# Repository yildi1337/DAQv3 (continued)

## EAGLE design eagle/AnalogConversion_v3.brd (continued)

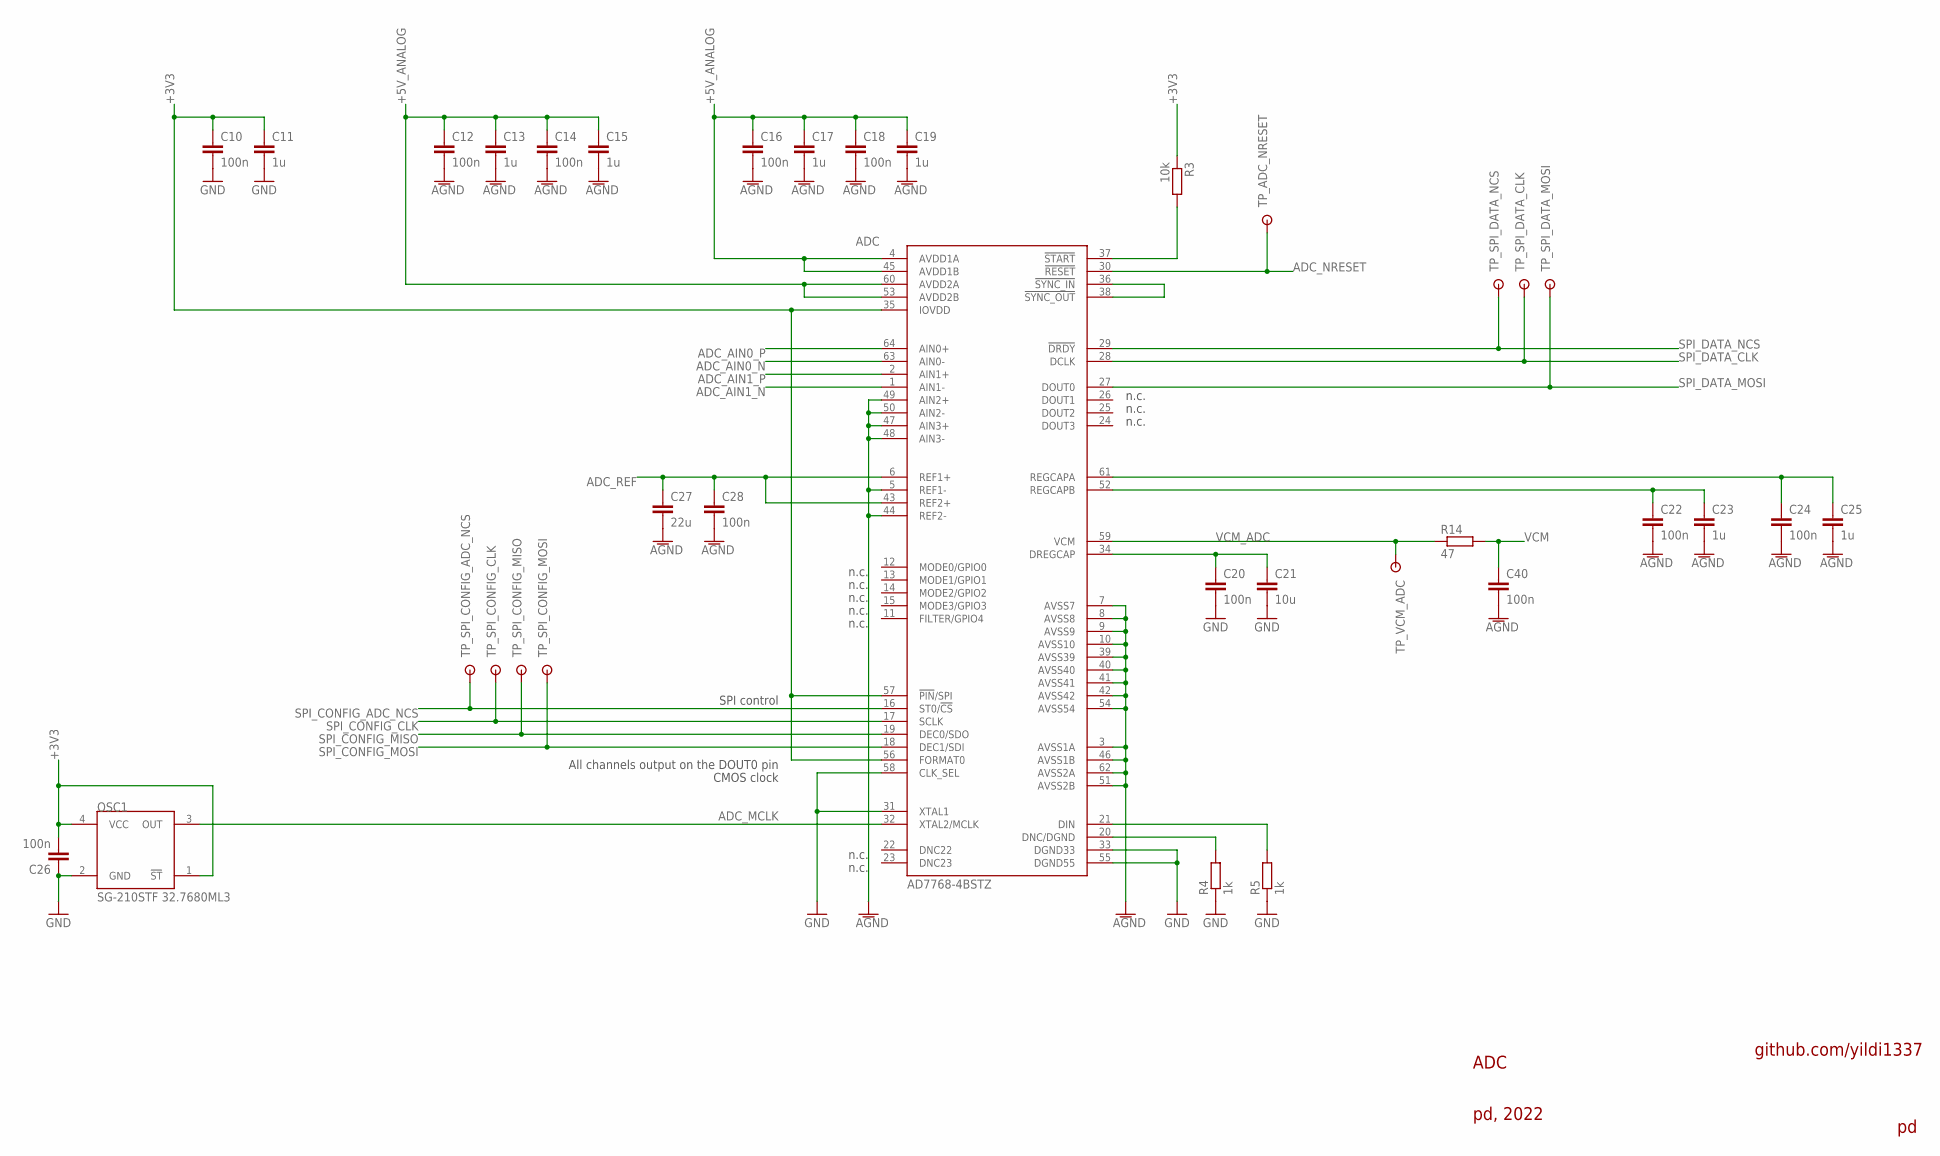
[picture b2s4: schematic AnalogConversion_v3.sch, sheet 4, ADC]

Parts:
ADC: AD7768-4BSTZ
C10, C12, C14, C16, C18, C20, C22, C24, C26, C28, C40: 100n; C0603
C11, C13, C15, C17, C19, C23, C25: 1u; C0603
C21: 10u; C0603
C27: 22u; C1206
OSC1: SG-210STF 32.7680ML3; SG-210STF-32.7680ML3
R3: 10k; R0603
R4, R5: 1k; R0603
R14: 47; R0603
TP_ADC_NRESET: RSPRO-1MM-TERMINAL-POST-2622034
TP_SPI_CONFIG_ADC_NCS: RSPRO-1MM-TERMINAL-POST-2622034
TP_SPI_CONFIG_CLK: RSPRO-1MM-TERMINAL-POST-2622034
TP_SPI_CONFIG_MISO: RSPRO-1MM-TERMINAL-POST-2622034
TP_SPI_CONFIG_MOSI: RSPRO-1MM-TERMINAL-POST-2622034
TP_SPI_DATA_CLK: RSPRO-1MM-TERMINAL-POST-2622034
TP_SPI_DATA_MOSI: RSPRO-1MM-TERMINAL-POST-2622034
TP_SPI_DATA_NCS: RSPRO-1MM-TERMINAL-POST-2622034
TP_VCM_ADC: RSPRO-1MM-TERMINAL-POST-2622034

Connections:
+3V3: ADC.35 (IOVDD), ADC.56 (FORMAT0), ADC.57 (!PIN!/SPI), C10.1, C11.1, C26.2, OSC1.1 (!ST), OSC1.4 (VCC), R3.1; also elsewhere on the board
+5V_ANALOG: ADC.4 (AVDD1A), ADC.45 (AVDD1B), ADC.53 (AVDD2B), ADC.60 (AVDD2A), C12.1, C13.1, C14.1, C15.1, C16.1, C17.1, C18.1, C19.1; also elsewhere on the board
ADC_AIN0_N: ADC.63 (AIN0-); also elsewhere on the board
ADC_AIN0_P: ADC.64 (AIN0+); also elsewhere on the board
ADC_AIN1_N: ADC.1 (AIN1-); also elsewhere on the board
ADC_AIN1_P: ADC.2 (AIN1+); also elsewhere on the board
ADC_MCLK: ADC.32 (XTAL2/MCLK), OSC1.3 (OUT)
ADC_NRESET: ADC.30 (!RESET!), TP_ADC_NRESET.P$1; also elsewhere on the board
ADC_REF: ADC.6 (REF1+), ADC.43 (REF2+), C27.1, C28.1; also elsewhere on the board
AGND: ADC.3 (AVSS1A), ADC.5 (REF1-), ADC.7 (AVSS7), ADC.8 (AVSS8), ADC.9 (AVSS9), ADC.10 (AVSS10), ADC.39 (AVSS39), ADC.40 (AVSS40), ADC.41 (AVSS41), ADC.42 (AVSS42), ADC.44 (REF2-), ADC.46 (AVSS1B), ADC.47 (AIN3+), ADC.48 (AIN3-), ADC.49 (AIN2+), ADC.50 (AIN2-), ADC.51 (AVSS2B), ADC.54 (AVSS54), ADC.62 (AVSS2A), C12.2, C13.2, C14.2, C15.2, C16.2, C17.2, C18.2, C19.2, C22.2, C23.2, C24.2, C25.2, C27.2, C28.2, C40.2; also elsewhere on the board
DIN: ADC.21 (DIN), R5.2
DNC/DGND: ADC.20 (DNC/DGND), R4.2
DREGCAP: ADC.34 (DREGCAP), C20.1, C21.1
GND: ADC.31 (XTAL1), ADC.33 (DGND33), ADC.55 (DGND55), ADC.58 (CLK_SEL), C10.2, C11.2, C20.2, C21.2, C26.1, OSC1.2 (GND), R4.1, R5.1; also elsewhere on the board
unnamed: ADC.36 (!SYNC_IN!), ADC.38 (!SYNC_OUT!)
unnamed: ADC.37 (!START!), R3.2
REGCAPA: ADC.61 (REGCAPA), C24.1, C25.1
REGCAPB: ADC.52 (REGCAPB), C22.1, C23.1
SPI_CONFIG_ADC_NCS: ADC.16 (ST0/!CS!), TP_SPI_CONFIG_ADC_NCS.P$1; also elsewhere on the board
SPI_CONFIG_CLK: ADC.17 (SCLK), TP_SPI_CONFIG_CLK.P$1; also elsewhere on the board
SPI_CONFIG_MISO: ADC.19 (DEC0/SDO), TP_SPI_CONFIG_MISO.P$1; also elsewhere on the board
SPI_CONFIG_MOSI: ADC.18 (DEC1/SDI), TP_SPI_CONFIG_MOSI.P$1; also elsewhere on the board
SPI_DATA_CLK: ADC.28 (DCLK), TP_SPI_DATA_CLK.P$1; also elsewhere on the board
SPI_DATA_MOSI: ADC.27 (DOUT0), TP_SPI_DATA_MOSI.P$1; also elsewhere on the board
SPI_DATA_NCS: ADC.29 (!DRDY!), TP_SPI_DATA_NCS.P$1; also elsewhere on the board
VCM: C40.1, R14.2; also elsewhere on the board
VCM_ADC: ADC.59 (VCM), R14.1, TP_VCM_ADC.P$1

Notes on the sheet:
ADC
pd, 2022
All channels output on the DOUT0 pin
CMOS clock
n.c.
SPI control
github.com/yildi1337

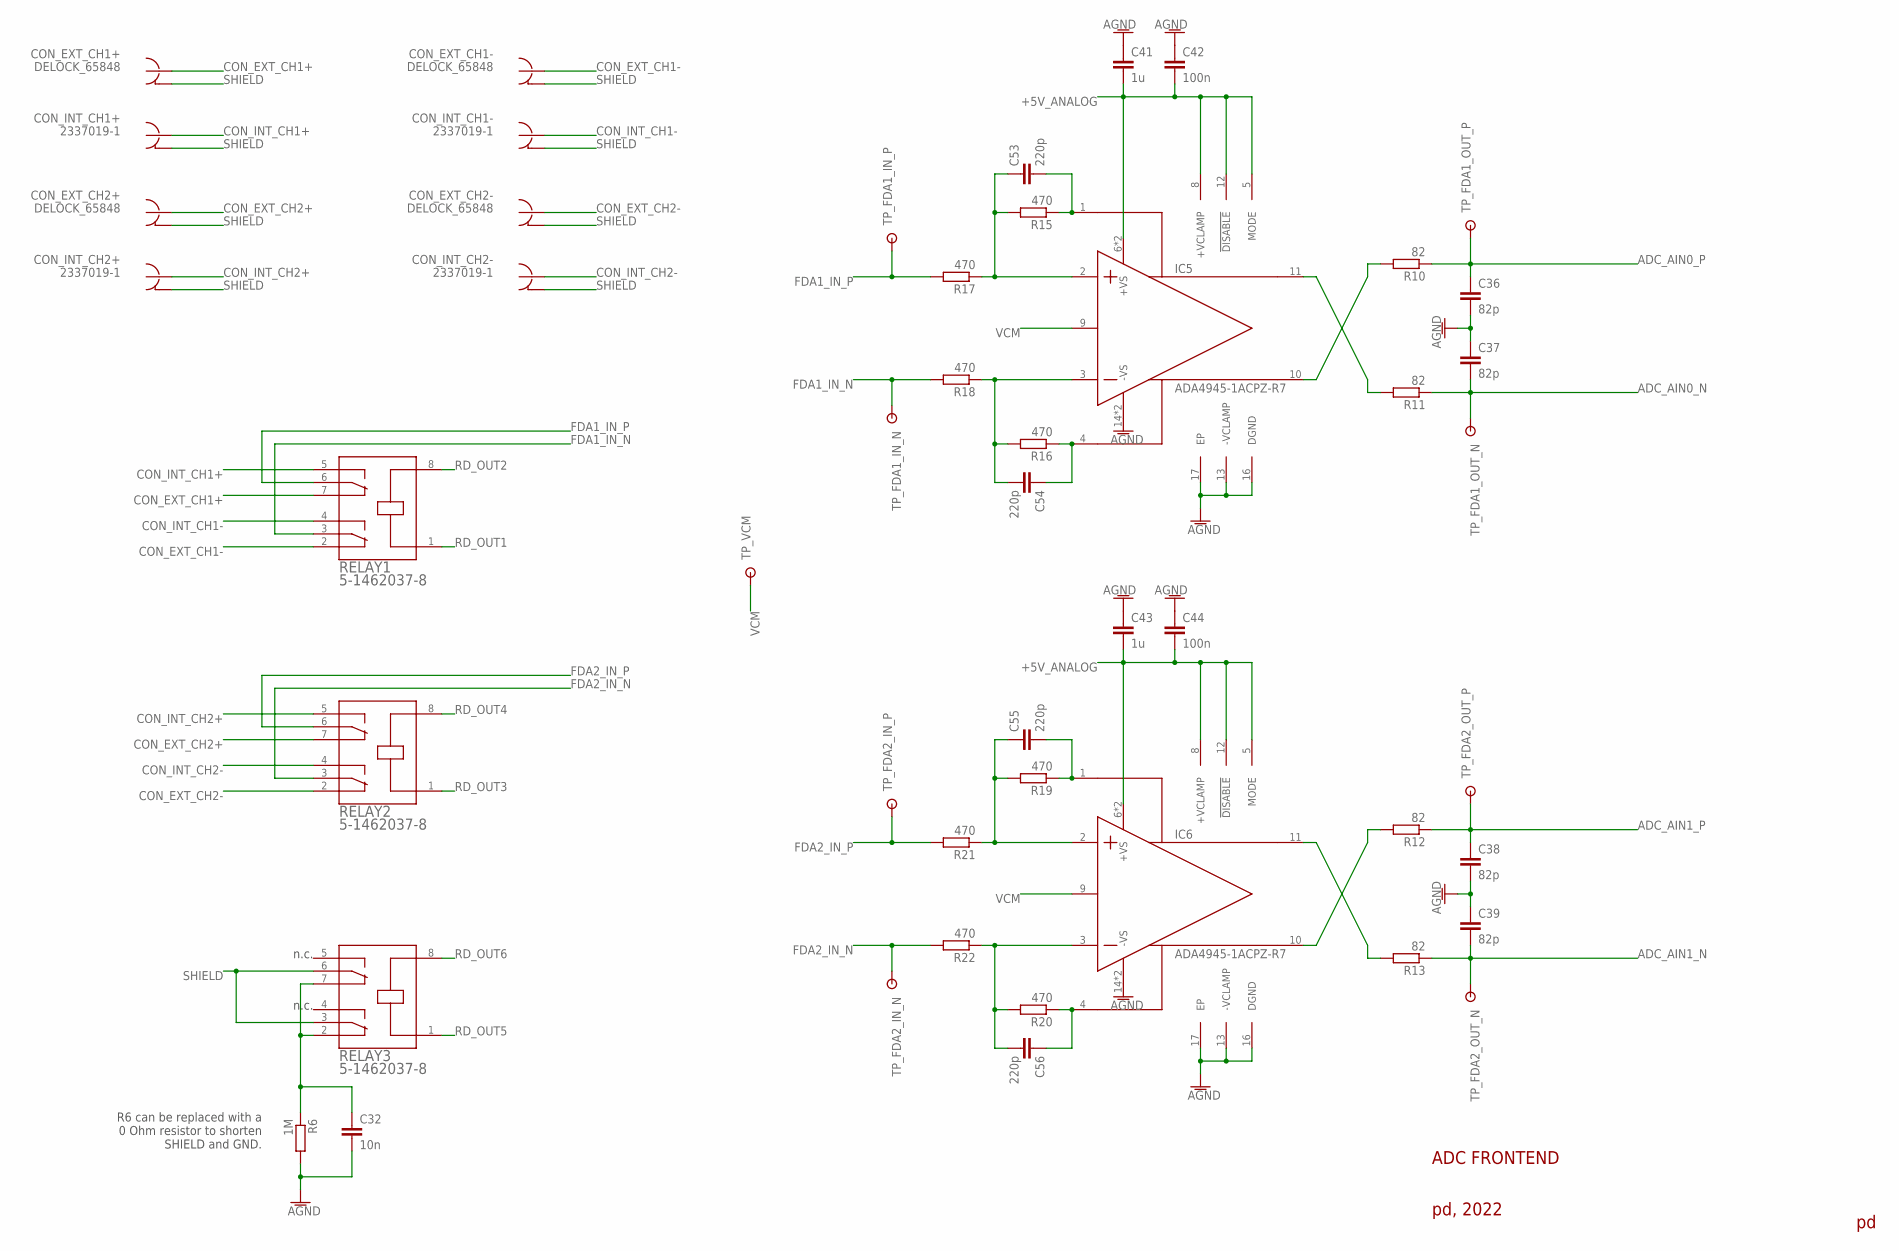
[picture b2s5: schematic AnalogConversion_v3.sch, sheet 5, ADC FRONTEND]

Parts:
C32: 10n; C0603
C36, C37, C38, C39: 82p; C0603
C41, C43: 1u; C0603
C42, C44: 100n; C0603
C53, C54, C55, C56: 220p; C0603
CON_EXT_CH1+, CON_EXT_CH1-, CON_EXT_CH2+, CON_EXT_CH2-: DELOCK_65848
CON_INT_CH1+, CON_INT_CH1-, CON_INT_CH2+, CON_INT_CH2-: 2337019-1
IC5, IC6: ADA4945-1ACPZ-R7
R6: 1M; R0603
R10, R11, R12, R13: 82; R0603
R15, R16, R17, R18, R19, R20, R21, R22: 470; R0603
RELAY1, RELAY2, RELAY3: 5-1462037-8
TP_FDA1_IN_N, TP_FDA1_IN_P, TP_FDA1_OUT_N, TP_FDA1_OUT_P, TP_FDA2_IN_N, TP_FDA2_IN_P, TP_FDA2_OUT_N, TP_FDA2_OUT_P: RSPRO-1MM-TERMINAL-POST-2622034
TP_VCM: RSPRO-1MM-TERMINAL-POST-2622034

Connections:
+5V_ANALOG: C41.2, C42.2, C43.2, C44.2, IC5.5 (MODE), IC5.6 (+VS), IC5.7 (+VS), IC5.8 (+VCLAMP), IC5.12 (!DISABLE), IC6.5 (MODE), IC6.6 (+VS), IC6.7 (+VS), IC6.8 (+VCLAMP), IC6.12 (!DISABLE); also elsewhere on the board
ADC_AIN0_N: C37.2, R11.1, TP_FDA1_OUT_N.P$1; also elsewhere on the board
ADC_AIN0_P: C36.1, R10.1, TP_FDA1_OUT_P.P$1; also elsewhere on the board
ADC_AIN1_N: C39.2, R13.1, TP_FDA2_OUT_N.P$1; also elsewhere on the board
ADC_AIN1_P: C38.1, R12.1, TP_FDA2_OUT_P.P$1; also elsewhere on the board
AGND: C32.2, C36.2, C37.1, C38.2, C39.1, C41.1, C42.1, C43.1, C44.1, IC5.13 (-VCLAMP), IC5.14 (-VS), IC5.15 (-VS), IC5.16 (DGND), IC5.17 (EP), IC6.13 (-VCLAMP), IC6.14 (-VS), IC6.15 (-VS), IC6.16 (DGND), IC6.17 (EP), R6.2; also elsewhere on the board
CON_EXT_CH1+: CON_EXT_CH1+.S, RELAY1.7
CON_EXT_CH1-: CON_EXT_CH1-.S, RELAY1.2
CON_EXT_CH2+: CON_EXT_CH2+.S, RELAY2.7
CON_EXT_CH2-: CON_EXT_CH2-.S, RELAY2.2
CON_INT_CH1+: CON_INT_CH1+.S (SIG), RELAY1.5
CON_INT_CH1-: CON_INT_CH1-.S (SIG), RELAY1.4
CON_INT_CH2+: CON_INT_CH2+.S (SIG), RELAY2.5
CON_INT_CH2-: CON_INT_CH2-.S (SIG), RELAY2.4
FDA1_IN_N: R18.2, RELAY1.3, TP_FDA1_IN_N.P$1
FDA1_IN_P: R17.2, RELAY1.6, TP_FDA1_IN_P.P$1
FDA2_IN_N: R22.2, RELAY2.3, TP_FDA2_IN_N.P$1
FDA2_IN_P: R21.2, RELAY2.6, TP_FDA2_IN_P.P$1
unnamed: C32.1, R6.1, RELAY3.2, RELAY3.7
unnamed: IC6.10 (+OUT), R12.2
unnamed: IC5.10 (+OUT), R10.2
unnamed: IC5.11 (-OUT), R11.2
unnamed: IC6.11 (-OUT), R13.2
unnamed: C53.1, IC5.2 (+IN), R15.2, R17.1
unnamed: C53.2, IC5.1 (-FB), R15.1
unnamed: C54.1, IC5.4 (+FB), R16.1
unnamed: C54.2, IC5.3 (-IN), R16.2, R18.1
unnamed: C55.1, IC6.2 (+IN), R19.2, R21.1
unnamed: C55.2, IC6.1 (-FB), R19.1
unnamed: C56.2, IC6.3 (-IN), R20.2, R22.1
unnamed: C56.1, IC6.4 (+FB), R20.1
RD_OUT1: RELAY1.1; also elsewhere on the board
RD_OUT2: RELAY1.8; also elsewhere on the board
RD_OUT3: RELAY2.1; also elsewhere on the board
RD_OUT4: RELAY2.8; also elsewhere on the board
RD_OUT5: RELAY3.1; also elsewhere on the board
RD_OUT6: RELAY3.8; also elsewhere on the board
SHIELD: CON_EXT_CH1+.G1 (G), CON_EXT_CH1+.G2 (G), CON_EXT_CH1+.G3 (G), CON_EXT_CH1+.G4 (G), CON_EXT_CH1-.G1 (G), CON_EXT_CH1-.G2 (G), CON_EXT_CH1-.G3 (G), CON_EXT_CH1-.G4 (G), CON_EXT_CH2+.G1 (G), CON_EXT_CH2+.G2 (G), CON_EXT_CH2+.G3 (G), CON_EXT_CH2+.G4 (G), CON_EXT_CH2-.G1 (G), CON_EXT_CH2-.G2 (G), CON_EXT_CH2-.G3 (G), CON_EXT_CH2-.G4 (G), CON_INT_CH1+.G1 (GND), CON_INT_CH1+.G2 (GND), CON_INT_CH1-.G1 (GND), CON_INT_CH1-.G2 (GND), CON_INT_CH2+.G1 (GND), CON_INT_CH2+.G2 (GND), CON_INT_CH2-.G1 (GND), CON_INT_CH2-.G2 (GND), RELAY3.3, RELAY3.6; also elsewhere on the board
VCM: IC5.9 (VOCM), IC6.9 (VOCM), TP_VCM.P$1; also elsewhere on the board

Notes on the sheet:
ADC FRONTEND
pd, 2022
n.c.
R6 can be replaced with a 0 Ohm resistor to shorten SHIELD and GND.

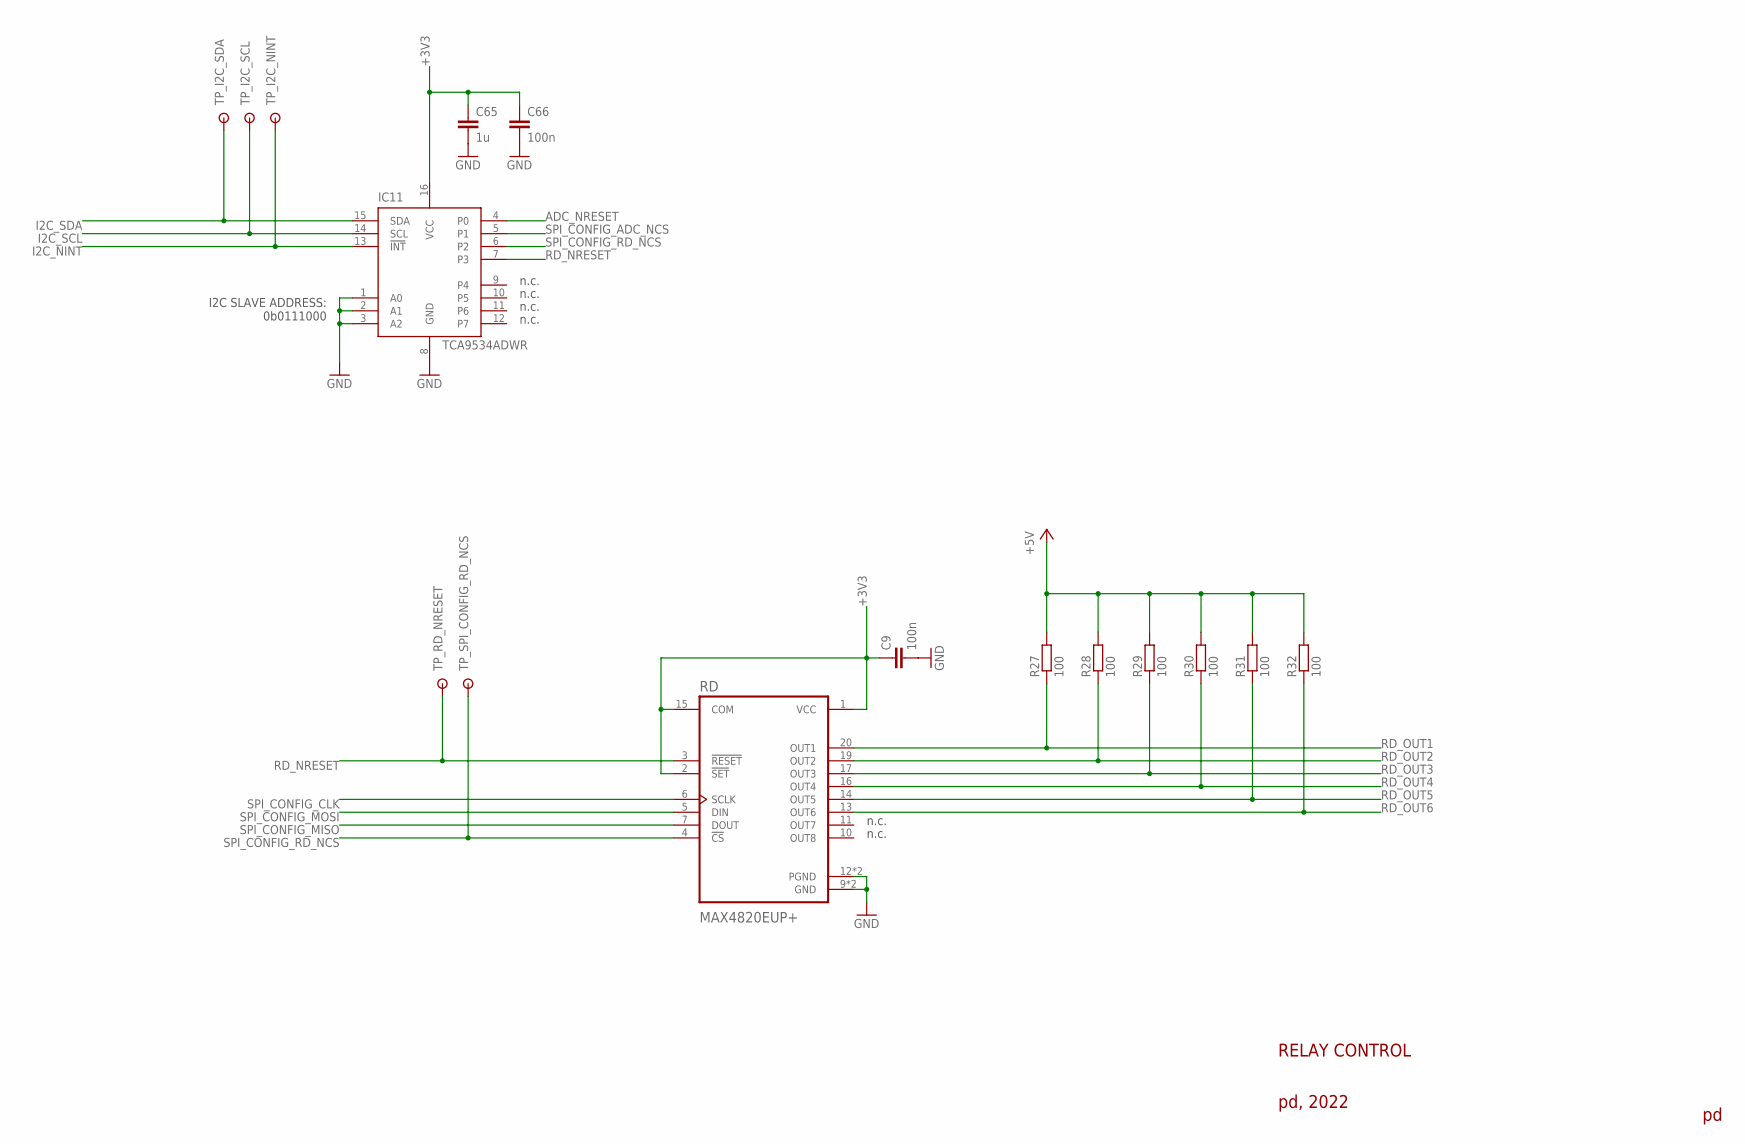
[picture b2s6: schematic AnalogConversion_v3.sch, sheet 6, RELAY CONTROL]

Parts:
C9, C66: 100n; C0603
C65: 1u; C0603
IC11: TCA9534ADWR
R27, R28, R29, R30, R31, R32: 100; R0603
RD: MAX4820EUP+
TP_I2C_NINT, TP_I2C_SCL, TP_I2C_SDA: RSPRO-1MM-TERMINAL-POST-2622034
TP_RD_NRESET: RSPRO-1MM-TERMINAL-POST-2622034
TP_SPI_CONFIG_RD_NCS: RSPRO-1MM-TERMINAL-POST-2622034

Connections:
+3V3: C9.1, C65.1, C66.1, IC11.16 (VCC), RD.1 (VCC), RD.2 (!SET), RD.15 (COM); also elsewhere on the board
+5V: R27.2, R28.2, R29.2, R30.2, R31.2, R32.2; also elsewhere on the board
ADC_NRESET: IC11.4 (P0); also elsewhere on the board
GND: C9.2, C65.2, C66.2, IC11.1 (A0), IC11.2 (A1), IC11.3 (A2), IC11.8 (GND), RD.9 (GND), RD.12 (PGND), RD.18 (PGND), RD.21 (GND); also elsewhere on the board
I2C_NINT: IC11.13 (!INT), TP_I2C_NINT.P$1; also elsewhere on the board
I2C_SCL: IC11.14 (SCL), TP_I2C_SCL.P$1; also elsewhere on the board
I2C_SDA: IC11.15 (SDA), TP_I2C_SDA.P$1; also elsewhere on the board
RD_NRESET: IC11.7 (P3), RD.3 (!RESET), TP_RD_NRESET.P$1
RD_OUT1: R27.1, RD.20 (OUT1); also elsewhere on the board
RD_OUT2: R28.1, RD.19 (OUT2); also elsewhere on the board
RD_OUT3: R29.1, RD.17 (OUT3); also elsewhere on the board
RD_OUT4: R30.1, RD.16 (OUT4); also elsewhere on the board
RD_OUT5: R31.1, RD.14 (OUT5); also elsewhere on the board
RD_OUT6: R32.1, RD.13 (OUT6); also elsewhere on the board
SPI_CONFIG_ADC_NCS: IC11.5 (P1); also elsewhere on the board
SPI_CONFIG_CLK: RD.6 (SCLK); also elsewhere on the board
SPI_CONFIG_MISO: RD.7 (DOUT); also elsewhere on the board
SPI_CONFIG_MOSI: RD.5 (DIN); also elsewhere on the board
SPI_CONFIG_RD_NCS: IC11.6 (P2), RD.4 (!CS), TP_SPI_CONFIG_RD_NCS.P$1

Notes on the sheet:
RELAY CONTROL
pd, 2022
n.c.
I2C SLAVE ADDRESS: 0b0111000

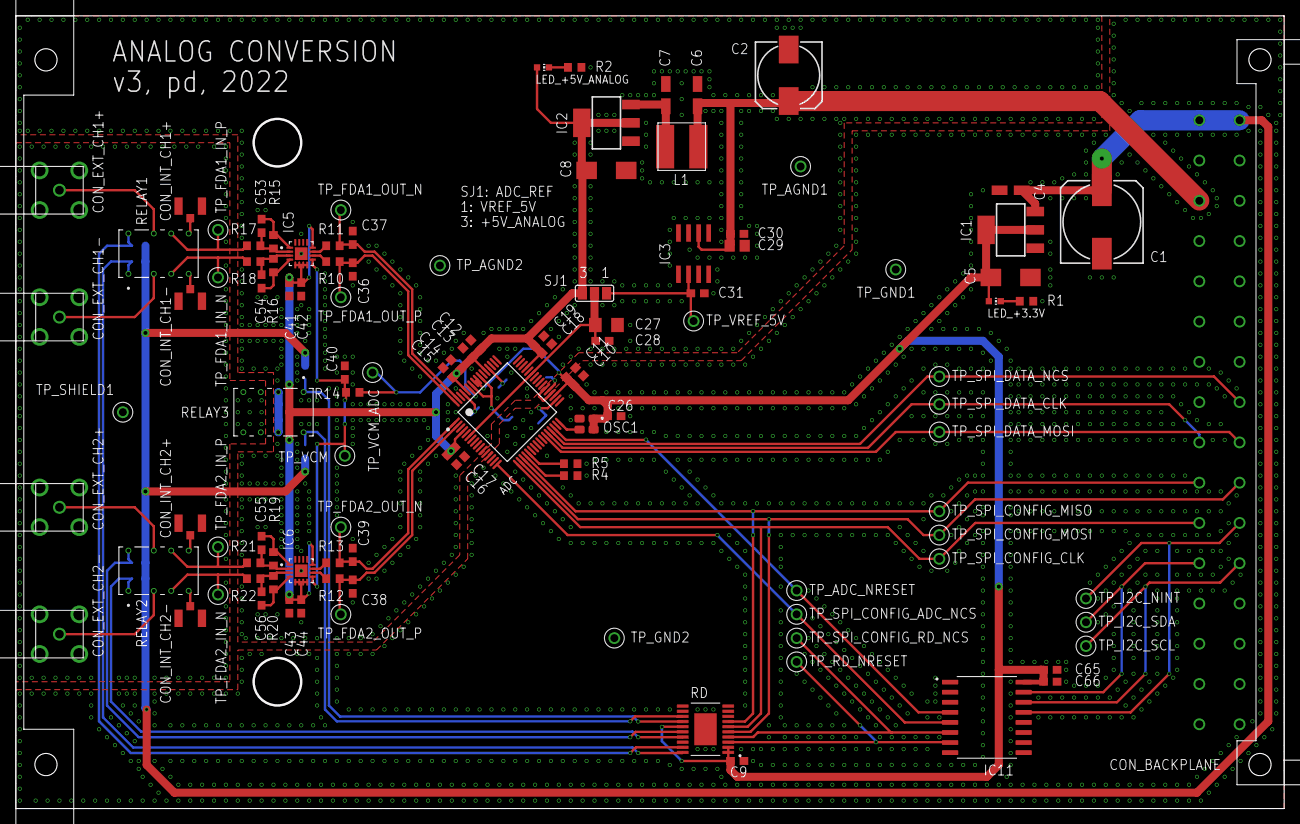
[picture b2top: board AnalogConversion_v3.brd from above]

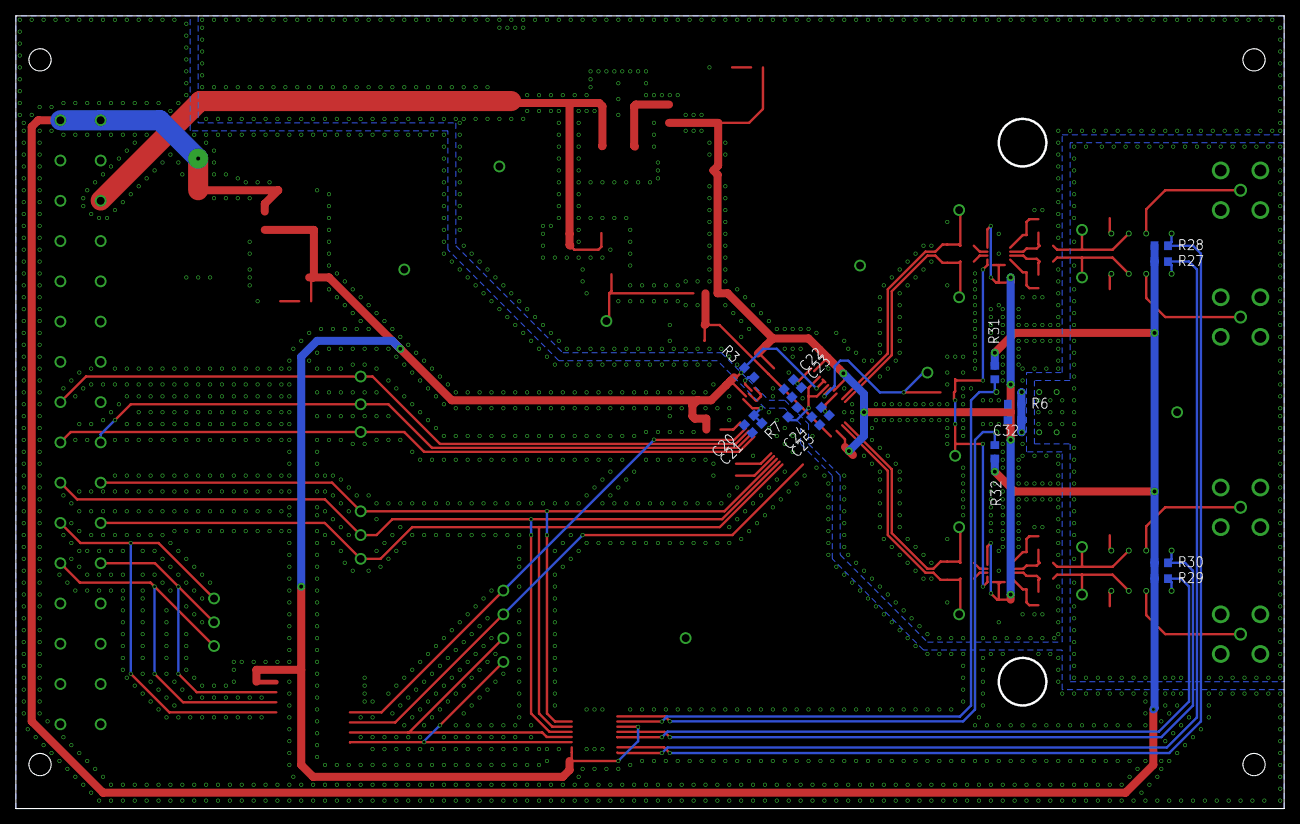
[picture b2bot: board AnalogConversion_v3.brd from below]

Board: 2 copper layers, 160.0 x 100.0 mm, 127 parts (16 on the bottom side), 70 nets.

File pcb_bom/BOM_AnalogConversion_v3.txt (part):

Stückliste exportiert aus D:/OneDrive/Elektronikprojekte/DAQ v3 STM32H7/Eagle/Analog Conversion v3/AnalogConversion_v3.sch am 25.07.2022 21:18

Qty Value                Device                          Package                         Parts                                                                                                                                                                                                                                                                                                                                                                                                                              Description                          POPULARITY SPICEPREFIX
2                        LEDCHIP-LED0603                 CHIP-LED0603                    LED_+3.3V, LED_+5V_ANALOG                                                                                                                                                                                                                                                                                                                                                                                                          LED                                  26                    
29                       RSPRO-1MM-TERMINAL-POST-2622034 RSPRO-1MM-TERMINAL-POST-2622034 TP_ADC_NRESET, TP_AGND1, TP_AGND2, TP_FDA1_IN_N, TP_FDA1_IN_P, TP_FDA1_OUT_N, TP_FDA1_OUT_P, TP_FDA2_IN_N, TP_FDA2_IN_P, TP_FDA2_OUT_N, TP_FDA2_OUT_P, TP_GND1, TP_GND2, TP_I2C_NINT, TP_I2C_SCL, TP_I2C_SDA, TP_RD_NRESET, TP_SHIELD1, TP_SPI_CONFIG_ADC_NCS, TP_SPI_CONFIG_CLK, TP_SPI_CONFIG_MISO, TP_SPI_CONFIG_MOSI, TP_SPI_CONFIG_RD_NCS, TP_SPI_DATA_CLK, TP_SPI_DATA_MOSI, TP_SPI_DATA_NCS, TP_VCM, TP_VCM_ADC, TP_VREF_5V                                                            
1                        SJ2W                            SJ_2                            SJ1                                                                                                                                                                                                                                                                                                                                                                                                                                SMD solder JUMPER                    7                     
1   0                    R-EU_R0603                      R0603                           R7                                                                                                                                                                                                                                                                                                                                                                                                                                 RESISTOR, European symbol            70         R          
1   09031326921          09031326921                     09031326921                     CON_BACKPLANE                                                                                                                                                                                                                                                                                                                                                                                                                                                                                 
1   1.8k                 R-EU_R0603                      R0603                           R2                                                                                                                                                                                                                                                                                                                                                                                                                                 RESISTOR, European symbol            70         R          
6   100                  R-EU_R0603                      R0603                           R27, R28, R29, R30, R31, R32                                                                                                                                                                                                                                                                                                                                                                                                       RESISTOR, European symbol            70         R          
1   1000u/16V            CPOL-EU153CLV-1010              153CLV-1010                     C1                                                                                                                                                                                                                                                                                                                                                                                                                                 POLARIZED CAPACITOR, European symbol 0          C          
17  100n                 C-EUC0603                       C0603                           C9, C10, C12, C14, C16, C18, C20, C22, C24, C26, C28, C30, C31, C40, C42, C44, C66                                                                                                                                                                                                                                                                                                                                                 CAPACITOR, European symbol           73         C          
1   100u                 VLS6045AF-101M                  VLS6045AF-101M                  L1                                                                                                                                                                                                                                                                                                                                                                                                                                                                                            
1   100u/25V             CPOL-EU153CLV-0810              153CLV-0810                     C2                                                                                                                                                                                                                                                                                                                                                                                                                                 POLARIZED CAPACITOR, European symbol 4          C          
1   10k                  R-EU_R0603                      R0603                           R3                                                                                                                                                                                                                                                                                                                                                                                                                                 RESISTOR, European symbol            70         R          
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
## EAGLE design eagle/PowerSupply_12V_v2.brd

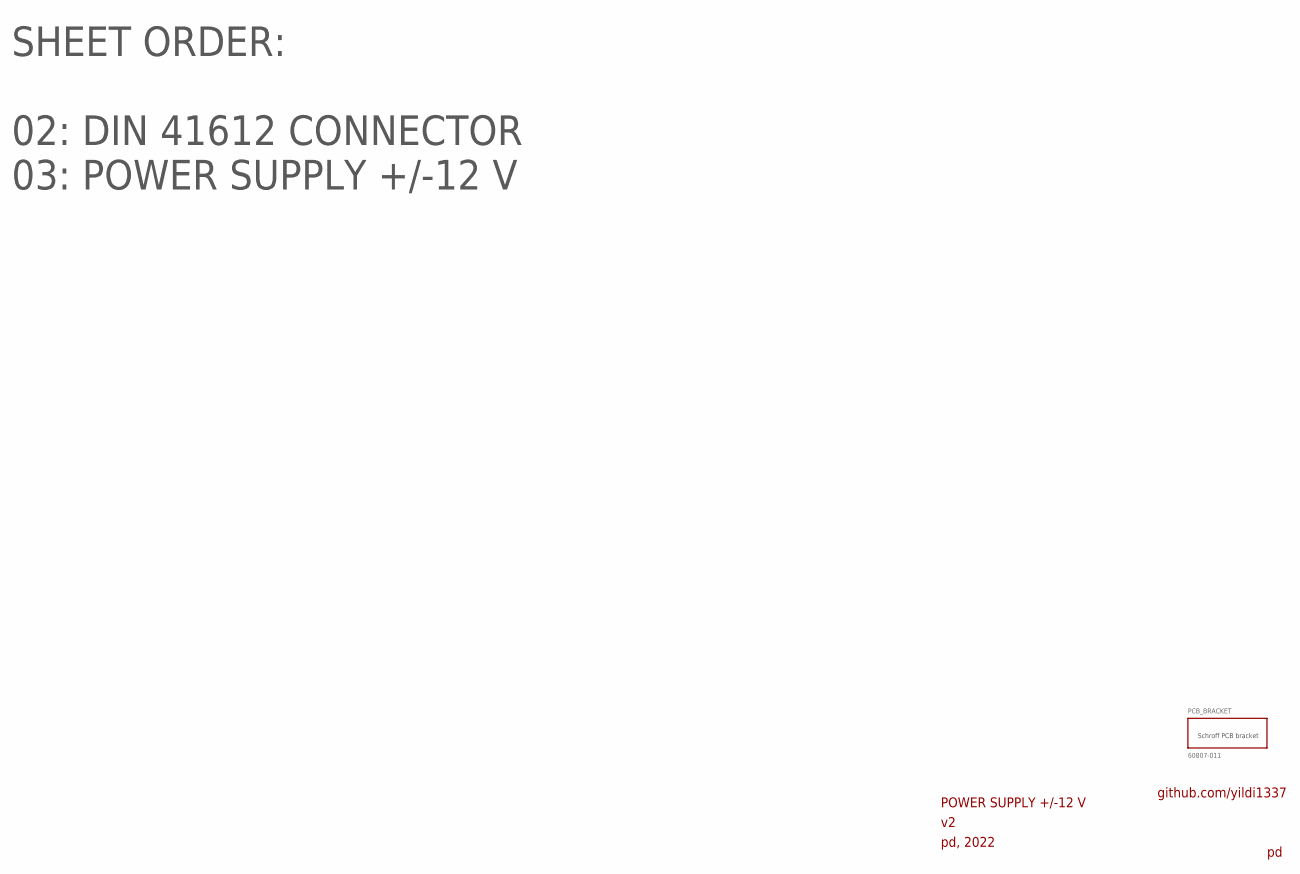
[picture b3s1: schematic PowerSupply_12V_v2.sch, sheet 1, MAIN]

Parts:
PCB_BRACKET: 60807-011

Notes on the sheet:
POWER SUPPLY +/-12 V
pd, 2022
github.com/yildi1337
SHEET ORDER: 02: DIN 41612 CONNECTOR 03: POWER SUPPLY +/-12 V

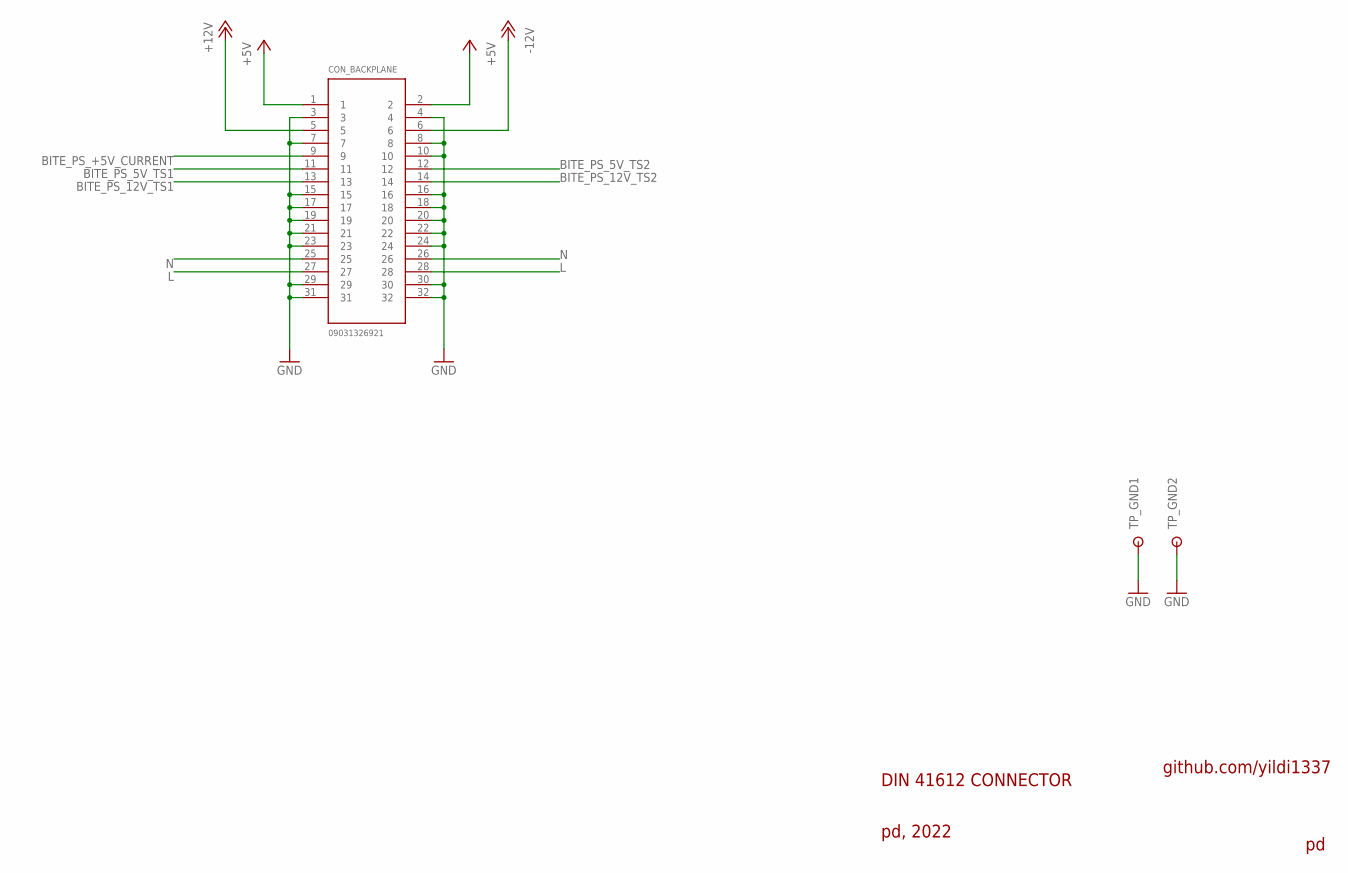
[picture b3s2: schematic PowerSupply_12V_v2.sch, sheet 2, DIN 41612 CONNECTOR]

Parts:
CON_BACKPLANE: 09031326921
TP_GND1, TP_GND2: RSPRO-1MM-TERMINAL-POST-2622034

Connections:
+5V: CON_BACKPLANE.1, CON_BACKPLANE.2
+12V: CON_BACKPLANE.5; also elsewhere on the board
-12V: CON_BACKPLANE.6; also elsewhere on the board
BITE_PS_5V_TS1: CON_BACKPLANE.11
BITE_PS_5V_TS2: CON_BACKPLANE.12
BITE_PS_12V_TS1: CON_BACKPLANE.13
BITE_PS_12V_TS2: CON_BACKPLANE.14
BITE_PS_+5V_CURRENT: CON_BACKPLANE.9
GND: CON_BACKPLANE.3, CON_BACKPLANE.4, CON_BACKPLANE.7, CON_BACKPLANE.8, CON_BACKPLANE.10, CON_BACKPLANE.15, CON_BACKPLANE.16, CON_BACKPLANE.17, CON_BACKPLANE.18, CON_BACKPLANE.19, CON_BACKPLANE.20, CON_BACKPLANE.21, CON_BACKPLANE.22, CON_BACKPLANE.23, CON_BACKPLANE.24, CON_BACKPLANE.29, CON_BACKPLANE.30, CON_BACKPLANE.31, CON_BACKPLANE.32, TP_GND1.P$1, TP_GND2.P$1; also elsewhere on the board
L: CON_BACKPLANE.27, CON_BACKPLANE.28; also elsewhere on the board
N: CON_BACKPLANE.25, CON_BACKPLANE.26; also elsewhere on the board

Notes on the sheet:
DIN 41612 CONNECTOR
pd, 2022
github.com/yildi1337
